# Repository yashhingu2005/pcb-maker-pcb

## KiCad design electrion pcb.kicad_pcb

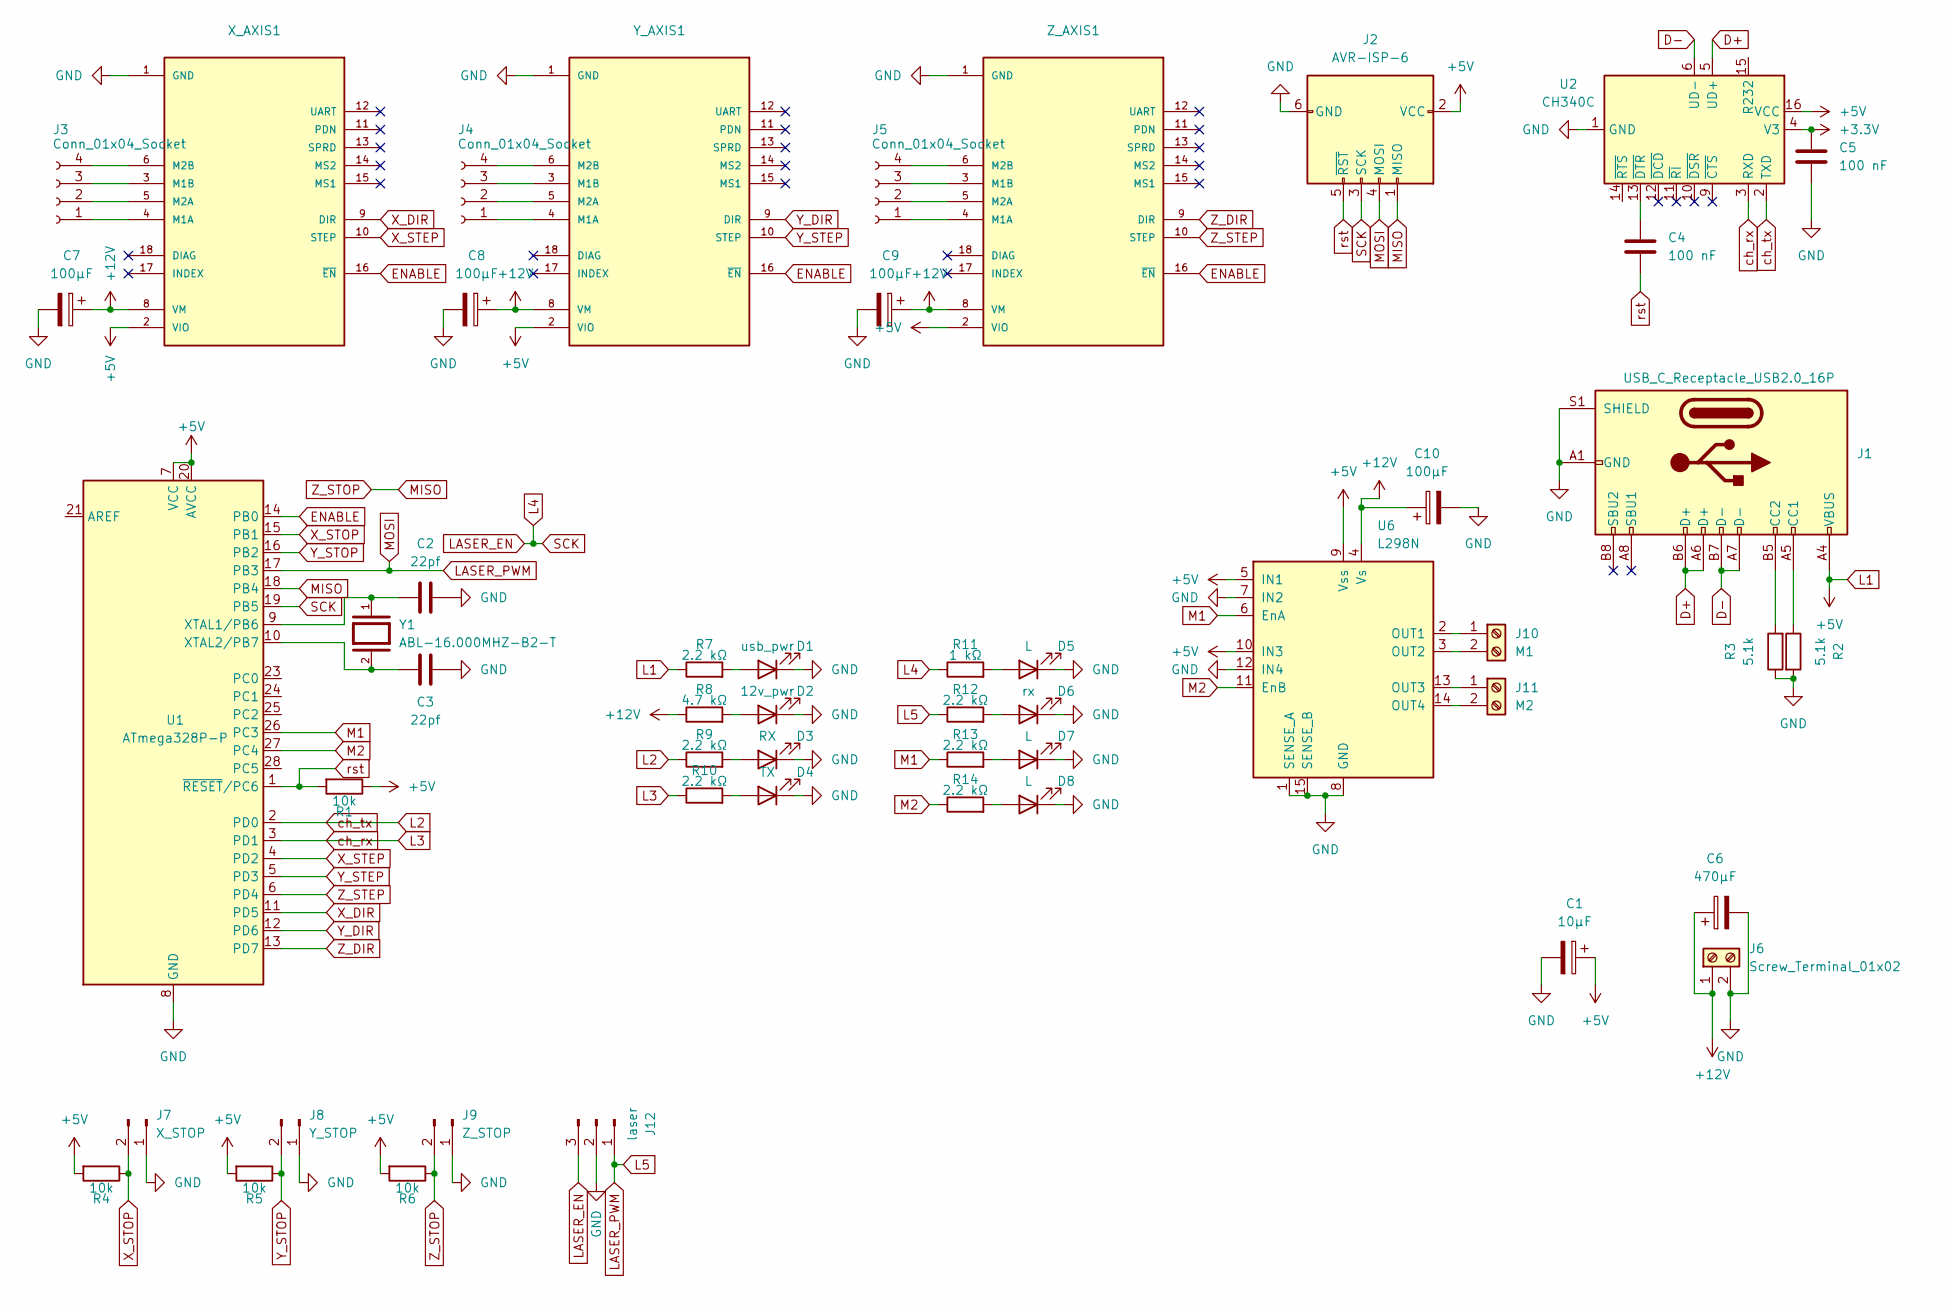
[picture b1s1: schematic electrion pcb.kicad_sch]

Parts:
C1: 10µF; CP_Radial_D5.0mm_P2.00mm
C2, C3: 22pf; C_Disc_D3.0mm_W1.6mm_P2.50mm
C4, C5: 100 nF; C_Disc_D3.0mm_W1.6mm_P2.50mm
C6: 470µF; CP_Radial_D5.0mm_P2.00mm
C7, C8, C9, C10: 100µF; CP_Radial_D5.0mm_P2.00mm
D1: usb_pwr; LED_D3.0mm
D2: 12v_pwr; LED_D3.0mm
D3: RX; LED_D3.0mm
D4: TX; LED_D3.0mm
D5, D7, D8: L; LED_D3.0mm
D6: rx; LED_D3.0mm
J1: USB_C_Receptacle_USB2.0_16P; USB_C_Receptacle_Palconn_UTC16-G
J2: AVR-ISP-6; IDC-Header_2x03_P2.54mm_Vertical
J3, J4, J5: Conn_01x04_Socket; JST_XH_B4B-XH-A_1x04_P2.50mm_Vertical
J6: Screw_Terminal_01x02; TerminalBlock_MaiXu_MX126-5.0-02P_1x02_P5.00mm
J7: X_STOP; PinHeader_1x02_P2.54mm_Vertical
J8: Y_STOP; PinHeader_1x02_P2.54mm_Vertical
J9: Z_STOP; PinHeader_1x02_P2.54mm_Vertical
J10: M1; TerminalBlock_MaiXu_MX126-5.0-02P_1x02_P5.00mm
J11: M2; TerminalBlock_MaiXu_MX126-5.0-02P_1x02_P5.00mm
J12: laser; PinHeader_1x03_P1.27mm_Vertical
R1, R4, R5, R6: 10k; R_Axial_DIN0207_L6.3mm_D2.5mm_P7.62mm_Horizontal
R2, R3: 5.1k; R_Axial_DIN0207_L6.3mm_D2.5mm_P7.62mm_Horizontal
R7, R9, R10, R12, R13, R14: 2.2 kΩ; R_Axial_DIN0207_L6.3mm_D2.5mm_P7.62mm_Horizontal
R8: 4.7 kΩ; R_Axial_DIN0207_L6.3mm_D2.5mm_P7.62mm_Horizontal
R11: 1 kΩ; R_Axial_DIN0207_L6.3mm_D2.5mm_P7.62mm_Horizontal
U1: ATmega328P-P; DIP-28_W7.62mm
U2: CH340C; SOIC-16_3.9x9.9mm_P1.27mm
U6: L298N; TO-220-15_P2.54x5.08mm_StaggerOdd_Lead4.58mm_Vertical
X_AXIS1: MODULE_TMC2209_SILENTSTEPSTICK; PARTREV 1.20
Y1: ABL-16.000MHZ-B2-T; XTAL_HC49P488W46L1150T500H350; PARTREV 03.27.2018
Y_AXIS1: MODULE_TMC2209_SILENTSTEPSTICK; PARTREV 1.20
Z_AXIS1: MODULE_TMC2209_SILENTSTEPSTICK; PARTREV 1.20

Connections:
+3.3V: C5.1, U2.4 (V3)
+12V: C6.1, C7.1, C8.1, C9.1, C10.1, J6.1, R8.1, U6.4 (Vs), X_AXIS1.8 (VM), Y_AXIS1.8 (VM), Z_AXIS1.8 (VM); also elsewhere on the board
D+: J1.A6 (D+), J1.B6 (D+), U2.5 (UD+)
D-: J1.A7 (D-), J1.B7 (D-), U2.6 (UD-)
ENABLE: U1.14 (PB0), X_AXIS1.16 (~EN), Y_AXIS1.16 (~EN), Z_AXIS1.16 (~EN); also elsewhere on the board
GND: C1.2, C2.2, C3.2, C5.2, C6.2, C7.2, C8.2, C9.2, C10.2, D1.1 (K), D2.1 (K), D3.1 (K), D4.1 (K), D5.1 (K), D6.1 (K), D7.1 (K), D8.1 (K), J1.A1 (GND), J1.A12 (GND), J1.B1 (GND), J1.B12 (GND), J1.S1 (SHIELD), J2.6 (GND), J6.2, J7.1, J8.1, J9.1, J12.2, R2.2, R3.1, U1.8 (GND), U1.22 (GND), U2.1 (GND), U6.1 (SENSE_A), U6.7 (IN2), U6.8 (GND), U6.12 (IN4), U6.15 (SENSE_B), X_AXIS1.1 (GND), X_AXIS1.7 (GND), Y_AXIS1.1 (GND), Y_AXIS1.7 (GND), Z_AXIS1.1 (GND), Z_AXIS1.7 (GND); also elsewhere on the board
L1: C1.1, J1.A4 (VBUS), J1.A9 (VBUS), J1.B4 (VBUS), J1.B9 (VBUS), J2.2 (VCC), R1.1, R4.2, R5.2, R6.2, R7.1, U1.7 (VCC), U1.20 (AVCC), U2.16 (VCC), U6.5 (IN1), U6.9 (Vss), U6.10 (IN3), X_AXIS1.2 (VIO), Y_AXIS1.2 (VIO), Z_AXIS1.2 (VIO); also elsewhere on the board
L2: R9.1, U1.2 (PD0), U2.2 (TXD)
L3: R10.1, U1.3 (PD1), U2.3 (RXD)
L4: J2.3 (SCK), J12.3, R11.1, U1.19 (PB5)
L5: J2.4 (MOSI), J12.1, R12.1, U1.17 (PB3)
M1: R13.1, U1.26 (PC3), U6.6 (EnA)
M2: R14.1, U1.27 (PC4), U6.11 (EnB)
MISO: J2.1 (MISO), J9.2, R6.1, U1.18 (PB4)
unnamed: D1.2 (A), R7.2
unnamed: D2.2 (A), R8.2
unnamed: D3.2 (A), R9.2
unnamed: D4.2 (A), R10.2
unnamed: D5.2 (A), R11.2
unnamed: D6.2 (A), R12.2
unnamed: D7.2 (A), R13.2
unnamed: D8.2 (A), R14.2
unnamed: J1.A5 (CC1), R2.1
unnamed: J1.B5 (CC2), R3.2
unnamed 24: J3.1, X_AXIS1.4 (M1A); also elsewhere on the board
unnamed 25: J3.2, X_AXIS1.5 (M2A); also elsewhere on the board
unnamed 26: J3.3, X_AXIS1.3 (M1B); also elsewhere on the board
unnamed 27: J3.4, X_AXIS1.6 (M2B); also elsewhere on the board
unnamed 28: J4.1, Y_AXIS1.4 (M1A); also elsewhere on the board
unnamed 29: J4.2, Y_AXIS1.5 (M2A); also elsewhere on the board
unnamed 30: J4.3, Y_AXIS1.3 (M1B); also elsewhere on the board
unnamed 31: J4.4, Y_AXIS1.6 (M2B); also elsewhere on the board
unnamed 32: J5.1, Z_AXIS1.4 (M1A); also elsewhere on the board
unnamed 33: J5.2, Z_AXIS1.5 (M2A); also elsewhere on the board
unnamed 34: J5.3, Z_AXIS1.3 (M1B); also elsewhere on the board
unnamed 35: J5.4, Z_AXIS1.6 (M2B); also elsewhere on the board
unnamed: J10.1, U6.2 (OUT1)
unnamed: J10.2, U6.3 (OUT2)
unnamed: J11.1, U6.13 (OUT3)
unnamed: J11.2, U6.14 (OUT4)
unnamed: C2.1, U1.9 (XTAL1/PB6), Y1.1
unnamed: C3.1, U1.10 (XTAL2/PB7), Y1.2
unnamed: C4.1, U2.13 (~DTR)
X_DIR: U1.11 (PD5), X_AXIS1.9 (DIR); also elsewhere on the board
X_STEP: U1.4 (PD2), X_AXIS1.10 (STEP); also elsewhere on the board
X_STOP: J7.2, R4.1, U1.15 (PB1)
Y_DIR: U1.12 (PD6), Y_AXIS1.9 (DIR); also elsewhere on the board
Y_STEP: U1.5 (PD3), Y_AXIS1.10 (STEP); also elsewhere on the board
Y_STOP: J8.2, R5.1, U1.16 (PB2)
Z_DIR: U1.13 (PD7), Z_AXIS1.9 (DIR); also elsewhere on the board
Z_STEP: U1.6 (PD4), Z_AXIS1.10 (STEP); also elsewhere on the board
rst: C4.2, J2.5 (~RST), R1.2, U1.1 (~RESET/PC6)

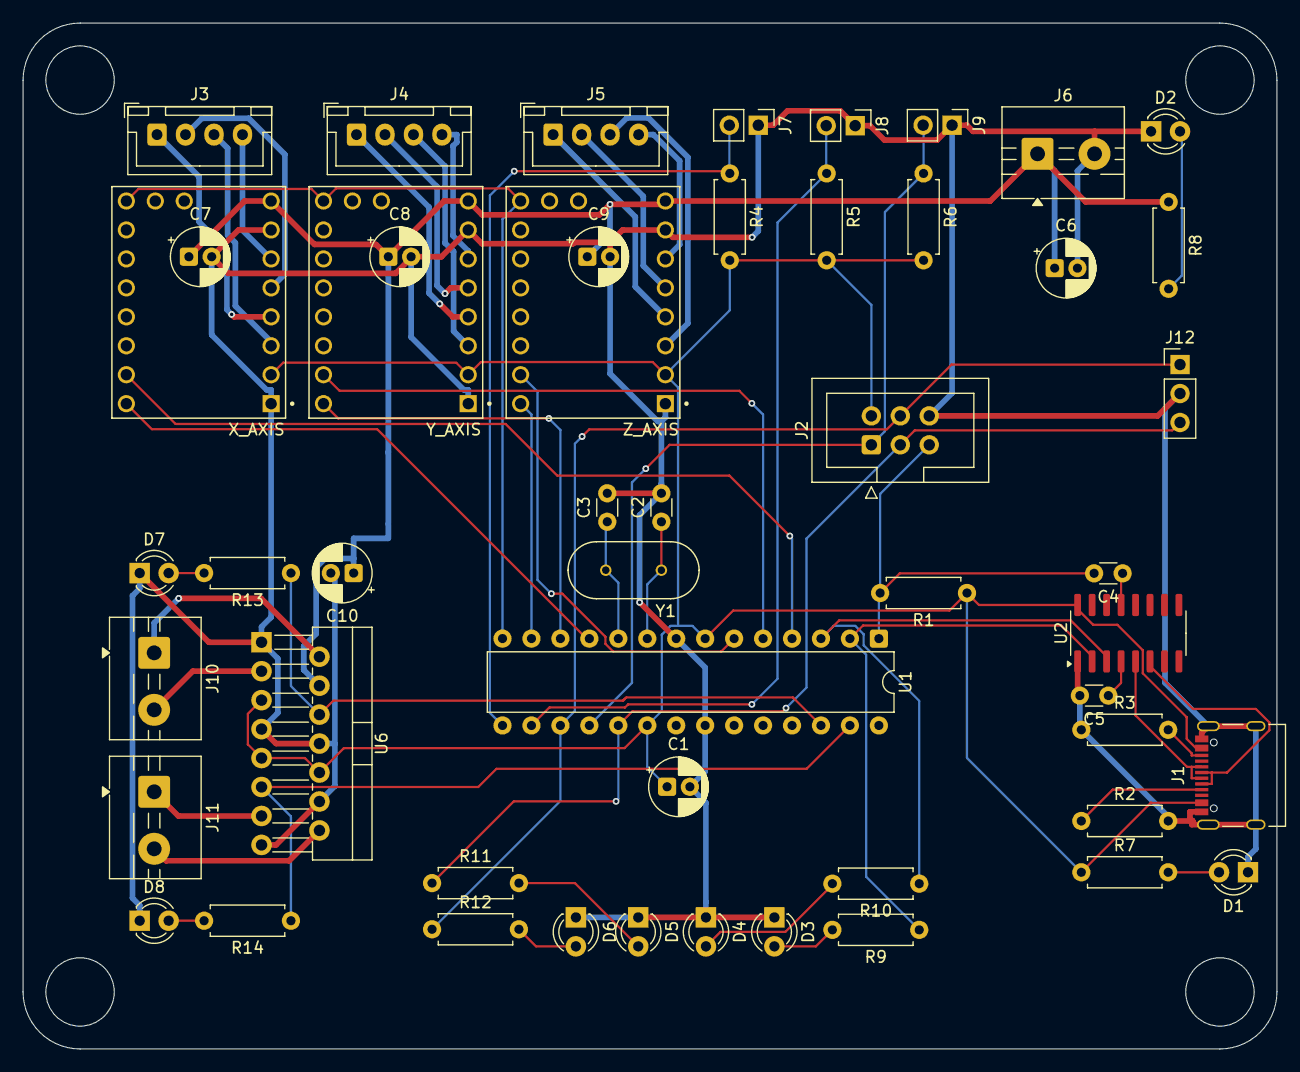
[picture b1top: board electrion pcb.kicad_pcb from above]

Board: 2 copper layers, 110.0 x 90.0 mm, 51 parts (0 on the bottom side), 52 nets.

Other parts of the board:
X_AXIS: MODULE_TMC2209_SILENTSTEPSTICK
Y_AXIS: MODULE_TMC2209_SILENTSTEPSTICK
Z_AXIS: MODULE_TMC2209_SILENTSTEPSTICK

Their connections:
+12V: X_AXIS.8 (VM), Y_AXIS.8 (VM), Z_AXIS.8 (VM); also elsewhere on the board
ENABLE: X_AXIS.16 (~EN), Y_AXIS.16 (~EN), Z_AXIS.16 (~EN); also elsewhere on the board
GND: X_AXIS.1 (GND), X_AXIS.7 (GND), Y_AXIS.1 (GND), Y_AXIS.7 (GND), Z_AXIS.1 (GND), Z_AXIS.7 (GND); also elsewhere on the board
L1: X_AXIS.2 (VIO), Y_AXIS.2 (VIO), Z_AXIS.2 (VIO); also elsewhere on the board
unnamed 24: X_AXIS.4 (M1A); also elsewhere on the board
unnamed 25: X_AXIS.5 (M2A); also elsewhere on the board
unnamed 26: X_AXIS.3 (M1B); also elsewhere on the board
unnamed 27: X_AXIS.6 (M2B); also elsewhere on the board
unnamed 28: Y_AXIS.4 (M1A); also elsewhere on the board
unnamed 29: Y_AXIS.5 (M2A); also elsewhere on the board
unnamed 30: Y_AXIS.3 (M1B); also elsewhere on the board
unnamed 31: Y_AXIS.6 (M2B); also elsewhere on the board
unnamed 32: Z_AXIS.4 (M1A); also elsewhere on the board
unnamed 33: Z_AXIS.5 (M2A); also elsewhere on the board
unnamed 34: Z_AXIS.3 (M1B); also elsewhere on the board
unnamed 35: Z_AXIS.6 (M2B); also elsewhere on the board
X_DIR: X_AXIS.9 (DIR); also elsewhere on the board
X_STEP: X_AXIS.10 (STEP); also elsewhere on the board
Y_DIR: Y_AXIS.9 (DIR); also elsewhere on the board
Y_STEP: Y_AXIS.10 (STEP); also elsewhere on the board
Z_DIR: Z_AXIS.9 (DIR); also elsewhere on the board
Z_STEP: Z_AXIS.10 (STEP); also elsewhere on the board
